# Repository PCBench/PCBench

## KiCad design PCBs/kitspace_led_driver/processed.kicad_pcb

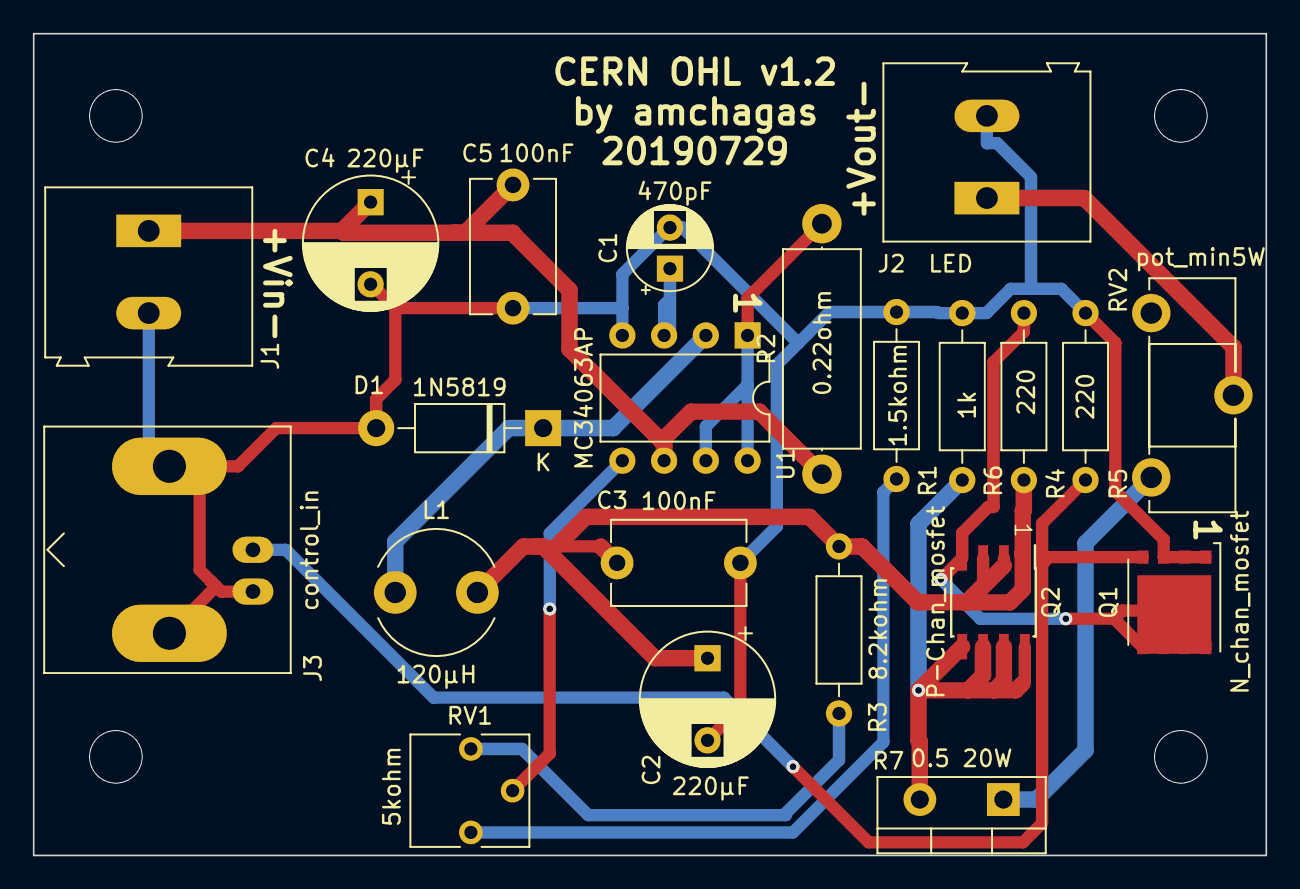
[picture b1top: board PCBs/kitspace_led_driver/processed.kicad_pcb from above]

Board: 2 copper layers, 75.0 x 50.0 mm, 26 parts (0 on the bottom side), 14 nets.

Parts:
C1: 470pF; CP_Radial_D5.0mm_P2.50mm
C2, C4: 220µF; CP_Radial_D8.0mm_P5.00mm
C3, C5: 100nF; C_Disc_D8.0mm_W5.0mm_P7.50mm
D1: 1N5819; D_DO-41_SOD81_P10.16mm_Horizontal
H1, H2, H3, H4: MountingHole; MountingHole_3.2mm_M3
J1: Vin; TerminalBlock_Altech_AK300-2_P5.00mm
J2: LED; TerminalBlock_Altech_AK300-2_P5.00mm
J3: control_in; BNC_Amphenol_B6252HB-NPP3G-50_Horizontal
L1: 120µH; L_Radial_D7.5mm_P5.00mm_Fastron_07P
Q1: N_chan_mosfet; TDSON-8-1
Q2: P-Chan_mosfet; SOIC-8_3.9x4.9mm_P1.27mm
R1: 1.5kohm; R_Axial_DIN0207_L6.3mm_D2.5mm_P10.16mm_Horizontal
R2: 0.22ohm; R_Axial_DIN0414_L11.9mm_D4.5mm_P15.24mm_Horizontal
R3: 8.2kohm; R_Axial_DIN0207_L6.3mm_D2.5mm_P10.16mm_Horizontal
R4, R5: 220; R_Axial_DIN0207_L6.3mm_D2.5mm_P10.16mm_Horizontal
R6: 1k; R_Axial_DIN0207_L6.3mm_D2.5mm_P10.16mm_Horizontal
R7: 0.5 20W; TO-220-2_Vertical
RV1: 5kohm; Potentiometer_Vishay_T73YP_Vertical
RV2: pot_min5W; Potentiometer_ACP_CA14-H5_Horizontal
U1: MC34063AP; DIP-8_W7.62mm

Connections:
GND: C1.2, C2.2, C3.1, C4.2, C5.2, D1.2, J1.2, J2.2, J3.2, Q1.1, Q1.2, Q1.3, R1.2, R5.1, R6.2, U1.4
unnamed: C1.1, U1.3
unnamed: C2.1, C3.2, L1.2, Q2.1, Q2.2, Q2.3, R3.1, R4.2
unnamed: D1.1, L1.1, U1.2
unnamed: J2.1, RV2.2
unnamed: J3.1, Q1.4, R5.2
unnamed: Q1.5, Q2.4, R4.1
unnamed: Q2.5, Q2.6, Q2.7, Q2.8, R6.1, R7.2
unnamed: R1.1, RV1.1
unnamed: R2.2, U1.1, U1.7, U1.8
unnamed: R3.2, RV1.3
unnamed: R7.1, RV2.3
unnamed: RV1.2, U1.5
VDD: C4.1, C5.1, J1.1, R2.1, U1.6

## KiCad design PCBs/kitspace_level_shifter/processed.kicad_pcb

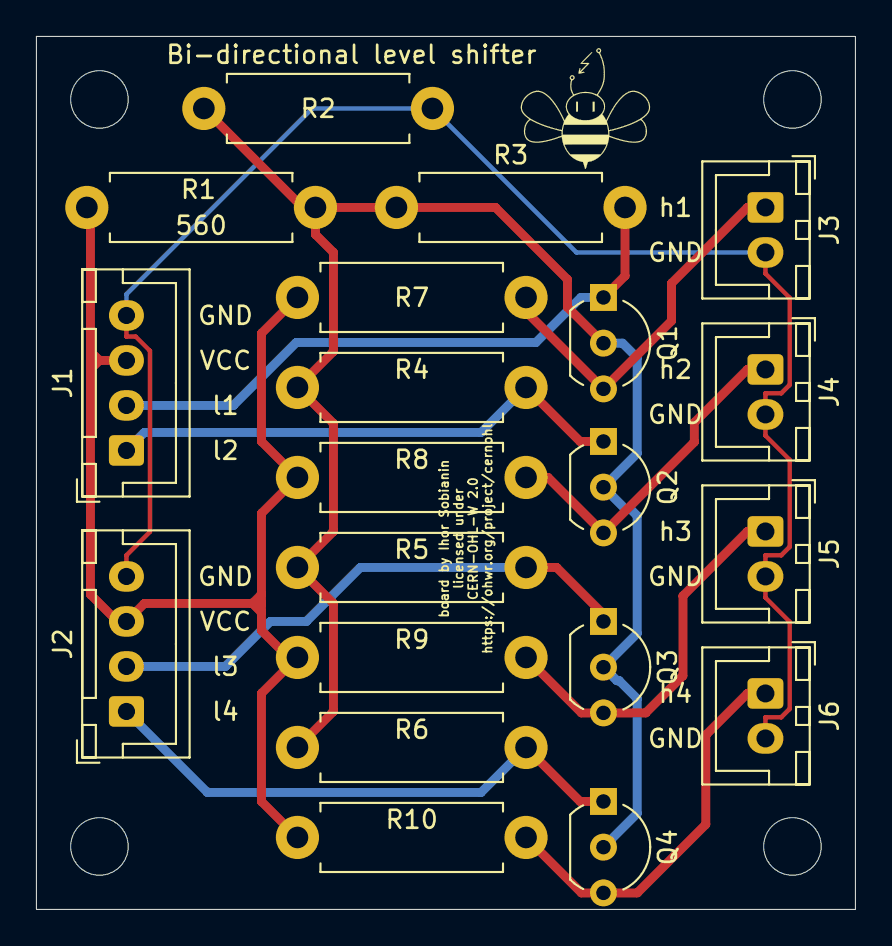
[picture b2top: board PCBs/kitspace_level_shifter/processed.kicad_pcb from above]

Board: 2 copper layers, 45.5 x 48.5 mm, 20 parts (0 on the bottom side), 11 nets.

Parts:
J1, J2: Conn_01x04; JST_XH_B4B-XH-A_1x04_P2.50mm_Vertical
J3, J4, J5, J6: Conn_01x02; JST_XH_B2B-XH-A_1x02_P2.50mm_Vertical
Q1, Q2, Q3, Q4: 2N7000; TO-92_Inline_Wide
R1: 560; R_Axial_DIN0411_L9.9mm_D3.6mm_P12.70mm_Horizontal
R2, R3, R4, R5, R6, R7, R8, R9, R10: 1k; R_Axial_DIN0411_L9.9mm_D3.6mm_P12.70mm_Horizontal

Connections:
+3V3: Q1.2, Q2.2, Q3.2, Q4.2, R1.1, R2.2, R3.1, R4.1, R5.1, R6.1
+5V: J1.3, J2.3, R1.2, R7.1, R8.1, R9.1, R10.1
GND: J1.4, J2.4, J3.2, J4.2, J5.2, J6.2, R2.1
d1_h: J3.1, Q1.3, R7.2
d1_l: J1.2, Q1.1, R3.2
d2_h: J4.1, Q2.3, R8.2
d2_l: J1.1, Q2.1, R4.2
d3_h: J5.1, Q3.3, R9.2
d3_l: J2.2, Q3.1, R5.2
d4_h: J6.1, Q4.3, R10.2
d4_l: J2.1, Q4.1, R6.2

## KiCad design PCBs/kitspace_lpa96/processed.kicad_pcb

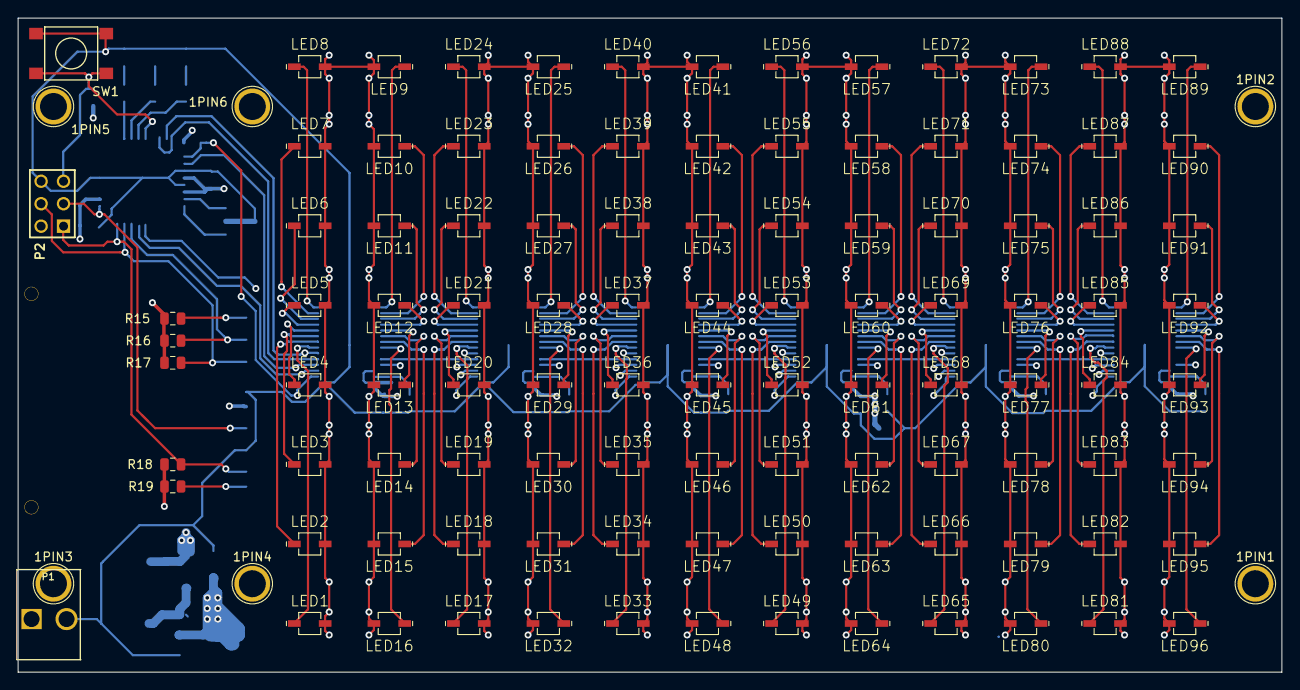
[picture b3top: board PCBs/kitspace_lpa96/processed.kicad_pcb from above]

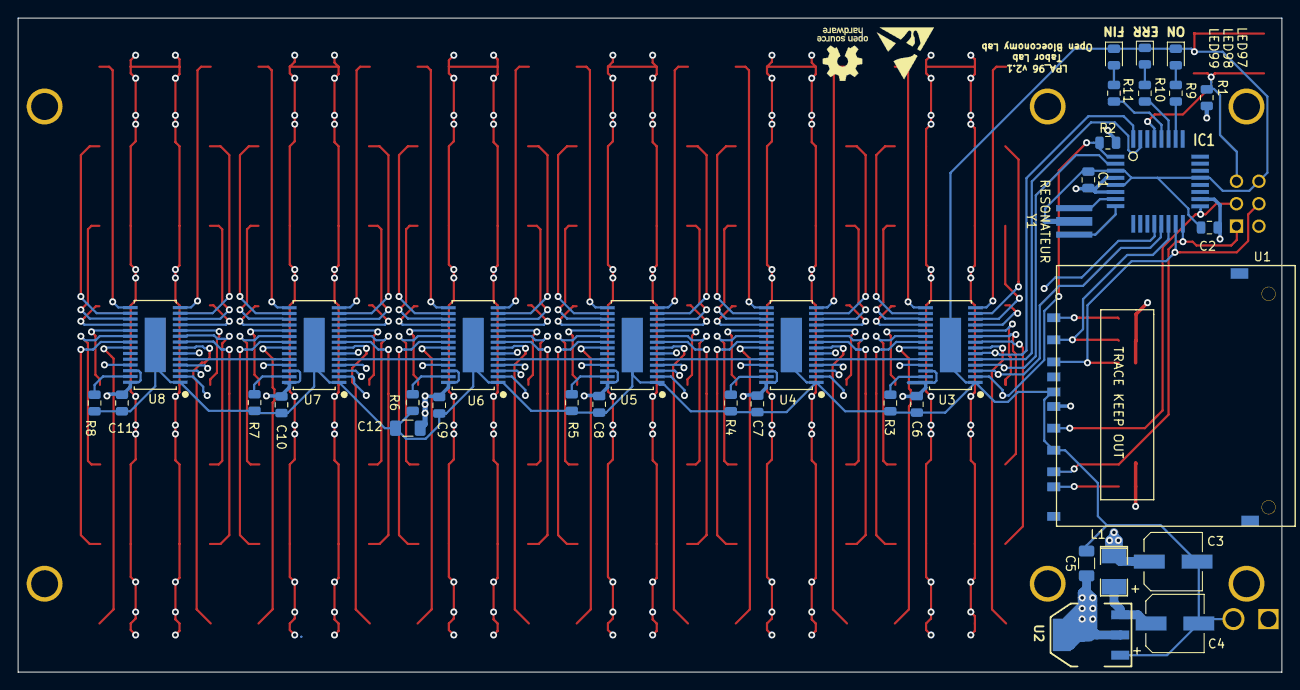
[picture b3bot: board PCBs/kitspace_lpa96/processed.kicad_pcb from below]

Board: 4 copper layers, 143.0 x 74.0 mm, 147 parts (37 on the bottom side), 132 nets.

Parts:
1PIN1, 1PIN2, 1PIN3, 1PIN4, 1PIN5, 1PIN6: P***; 1pin
C1, C2, C6, C7, C8, C9, C10, C11: 100nF; C_0805_2012Metric
C3, C4: 47uF; CP_Elec_6.3x5.3
C5, C12: 10uF; C_1206_3216Metric
IC1: ATMEGA328-A; TQFP32_FIXED
L1: 10uH; L-1210
LED1, LED2, LED3, LED4, LED5, LED6, LED7, LED8, LED9, LED10, LED11, LED12, LED13, LED14, LED15, LED16, LED17, LED18, LED19, LED20, LED21, LED22, LED23, LED24, LED25, LED26, LED27, LED28, LED29, LED30, LED31, LED32, LED33, LED34, LED35, LED36, LED37, LED38, LED39, LED40, LED41, LED42, LED43, LED44, LED45, LED46, LED47, LED48, LED49, LED50, LED51, LED52, LED53, LED54, LED55, LED56, LED57, LED58, LED59, LED60, LED61, LED62, LED63, LED64, LED65, LED66, LED67, LED68, LED69, LED70, LED71, LED72, LED73, LED74, LED75, LED76, LED77, LED78, LED79, LED80, LED81, LED82, LED83, LED84, LED85, LED86, LED87, LED88, LED89, LED90, LED91, LED92, LED93, LED94, LED95, LED96: LED_ALT; VLDx1232G
LED97, LED98, LED99: LED_ALT; LED_0805_2012Metric
P1: CONN_2; PIN_ARRAY_2X1_3960um
P2: CONN_3X2; pin_array_3x2
R1, R2: 10k; R_0805_2012Metric
R3, R4, R5, R6, R7, R8: 2.2k; R_0805_2012Metric
R9, R10, R11: 330R; R_0805_2012Metric
R15, R16, R17, R18, R19: 47k; R_0805_2012Metric
SW1: SW_PUSH; SW_PUSH_SMD
U1: SD_CARD; SD_CONN
U2: LD1117S33; SOT223
U3, U4, U5, U6, U7, U8: TLC5941; TLC5941_PWP_28
Y1: RESONATEUR; crystal_smd

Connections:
/BLANK: IC1.1, R2.1, U3.2, U4.2, U5.2, U6.2, U7.2, U8.2
/ERR: IC1.27, R10.1
/FIN: IC1.28, R11.1
/GSCLK: IC1.12, U3.25, U4.25, U5.25, U6.25, U7.25, U8.25
/MISO: IC1.16, P2.1, R18.2, U1.7
/MODE: IC1.32, U3.6, U4.6, U5.6, U6.6, U7.6, U8.6
/MOSI: IC1.15, P2.4, R17.2, U1.2
/ON: IC1.26, R9.1
/RST: IC1.29, P2.5, R1.1, SW1.1
/SCK: IC1.17, P2.3, U1.5
/SCLK: IC1.2, U3.4, U4.4, U5.4, U6.4, U7.4, U8.4
/SIN: IC1.31, U3.5
/SS: IC1.14, R16.2, U1.1
/VIN: C3.1, L1.1, LED1.2, LED2.2, LED3.2, LED4.2, LED5.2, LED6.2, LED7.2, LED8.2, LED9.2, LED10.2, LED11.2, LED12.2, LED13.2, LED14.2, LED15.2, LED16.2, LED17.2, LED18.2, LED19.2, LED20.2, LED21.2, LED22.2, LED23.2, LED24.2, LED25.2, LED26.2, LED27.2, LED28.2, LED29.2, LED30.2, LED31.2, LED32.2, LED33.2, LED34.2, LED35.2, LED36.2, LED37.2, LED38.2, LED39.2, LED40.2, LED41.2, LED42.2, LED43.2, LED44.2, LED45.2, LED46.2, LED47.2, LED48.2, LED49.2, LED50.2, LED51.2, LED52.2, LED53.2, LED54.2, LED55.2, LED56.2, LED57.2, LED58.2, LED59.2, LED60.2, LED61.2, LED62.2, LED63.2, LED64.2, LED65.2, LED66.2, LED67.2, LED68.2, LED69.2, LED70.2, LED71.2, LED72.2, LED73.2, LED74.2, LED75.2, LED76.2, LED77.2, LED78.2, LED79.2, LED80.2, LED81.2, LED82.2, LED83.2, LED84.2, LED85.2, LED86.2, LED87.2, LED88.2, LED89.2, LED90.2, LED91.2, LED92.2, LED93.2, LED94.2, LED95.2, LED96.2, P1.1
/XLAT: IC1.13, U3.3, U4.3, U5.3, U6.3, U7.3, U8.3
/lpa96_leds_drivers/SOUT1: U3.24, U4.5
/lpa96_leds_drivers/SOUT2: U4.24, U5.5
/lpa96_leds_drivers/SOUT3: U5.24, U6.5
/lpa96_leds_drivers/SOUT4: U6.24, U7.5
/lpa96_leds_drivers/SOUT5: U7.24, U8.5
GND: C1.1, C2.1, C3.2, C4.2, C5.2, C6.2, C7.2, C8.2, C9.2, C10.2, C11.2, C12.2, IC1.3, IC1.5, IC1.21, LED97.1, LED98.1, LED99.1, P1.2, P2.6, R3.1, R4.1, R5.1, R6.1, R7.1, R8.1, SW1.2, U1.3, U1.6, U2.1, U3.1, U3.29, U4.1, U4.29, U5.1, U5.29, U6.1, U6.29, U7.1, U7.29, U8.1, U8.29, Y1.2
unnamed: C4.1, L1.2, U2.3
unnamed: IC1.7, Y1.3
unnamed: IC1.8, Y1.1
unnamed: LED1.1, U3.7
unnamed: LED2.1, U3.8
unnamed: LED3.1, U3.9
unnamed: LED4.1, U3.10
unnamed: LED5.1, U3.11
unnamed: LED6.1, U3.12
unnamed: LED7.1, U3.13
unnamed: LED8.1, U3.14
unnamed: LED9.1, U3.15
unnamed: LED10.1, U3.16
unnamed: LED11.1, U3.17
unnamed: LED12.1, U3.18
unnamed: LED13.1, U3.19
unnamed: LED14.1, U3.20
unnamed: LED15.1, U3.21
unnamed: LED16.1, U3.22
unnamed: LED17.1, U4.7
unnamed: LED18.1, U4.8
unnamed: LED19.1, U4.9
unnamed: LED20.1, U4.10
unnamed: LED21.1, U4.11
unnamed: LED22.1, U4.12
unnamed: LED23.1, U4.13
unnamed: LED24.1, U4.14
unnamed: LED25.1, U4.15
unnamed: LED26.1, U4.16
unnamed: LED27.1, U4.17
unnamed: LED28.1, U4.18
unnamed: LED29.1, U4.19
unnamed: LED30.1, U4.20
unnamed: LED31.1, U4.21
unnamed: LED32.1, U4.22
unnamed: LED33.1, U5.7
unnamed: LED34.1, U5.8
unnamed: LED35.1, U5.9
unnamed: LED36.1, U5.10
unnamed: LED37.1, U5.11
unnamed: LED38.1, U5.12
unnamed: LED39.1, U5.13
unnamed: LED40.1, U5.14
unnamed: LED41.1, U5.15
unnamed: LED42.1, U5.16
unnamed: LED43.1, U5.17
unnamed: LED44.1, U5.18
unnamed: LED45.1, U5.19
unnamed: LED46.1, U5.20
unnamed: LED47.1, U5.21
unnamed: LED48.1, U5.22
unnamed: LED49.1, U6.7
unnamed: LED50.1, U6.8
unnamed: LED51.1, U6.9
unnamed: LED52.1, U6.10
unnamed: LED53.1, U6.11
unnamed: LED54.1, U6.12
unnamed: LED55.1, U6.13
unnamed: LED56.1, U6.14
unnamed: LED57.1, U6.15
unnamed: LED58.1, U6.16
unnamed: LED59.1, U6.17
unnamed: LED60.1, U6.18
unnamed: LED61.1, U6.19
unnamed: LED62.1, U6.20
unnamed: LED63.1, U6.21
unnamed: LED64.1, U6.22
unnamed: LED65.1, U7.7
unnamed: LED66.1, U7.8
unnamed: LED67.1, U7.9
unnamed: LED68.1, U7.10
unnamed: LED69.1, U7.11
unnamed: LED70.1, U7.12
unnamed: LED71.1, U7.13
unnamed: LED72.1, U7.14
unnamed: LED73.1, U7.15
unnamed: LED74.1, U7.16
unnamed: LED75.1, U7.17
unnamed: LED76.1, U7.18
unnamed: LED77.1, U7.19
unnamed: LED78.1, U7.20
unnamed: LED79.1, U7.21
unnamed: LED80.1, U7.22
unnamed: LED81.1, U8.7
unnamed: LED82.1, U8.8
unnamed: LED83.1, U8.9
unnamed: LED84.1, U8.10
unnamed: LED85.1, U8.11
unnamed: LED86.1, U8.12
unnamed: LED87.1, U8.13
unnamed: LED88.1, U8.14
unnamed: LED89.1, U8.15
unnamed: LED90.1, U8.16
unnamed: LED91.1, U8.17
unnamed: LED92.1, U8.18
unnamed: LED93.1, U8.19
unnamed: LED94.1, U8.20
unnamed: LED95.1, U8.21
unnamed: LED96.1, U8.22
unnamed: LED97.2, R9.2
unnamed: LED98.2, R10.2
unnamed: LED99.2, R11.2
unnamed: R3.2, U3.27
unnamed: R4.2, U4.27
unnamed: R5.2, U5.27
unnamed: R6.2, U6.27
unnamed: R7.2, U7.27
unnamed: R8.2, U8.27
unnamed: R15.2, U1.9
unnamed: R19.2, U1.8
VCC: C1.2, C2.2, C5.1, C6.1, C7.1, C8.1, C9.1, C10.1, C11.1, C12.1, IC1.4, IC1.6, IC1.18, P2.2, R1.2, R2.2, R15.1, R16.1, R17.1, R18.1, R19.1, U1.4, U2.2, U2.4, U3.26, U3.28, U4.26, U4.28, U5.26, U5.28, U6.26, U6.28, U7.26, U7.28, U8.26, U8.28

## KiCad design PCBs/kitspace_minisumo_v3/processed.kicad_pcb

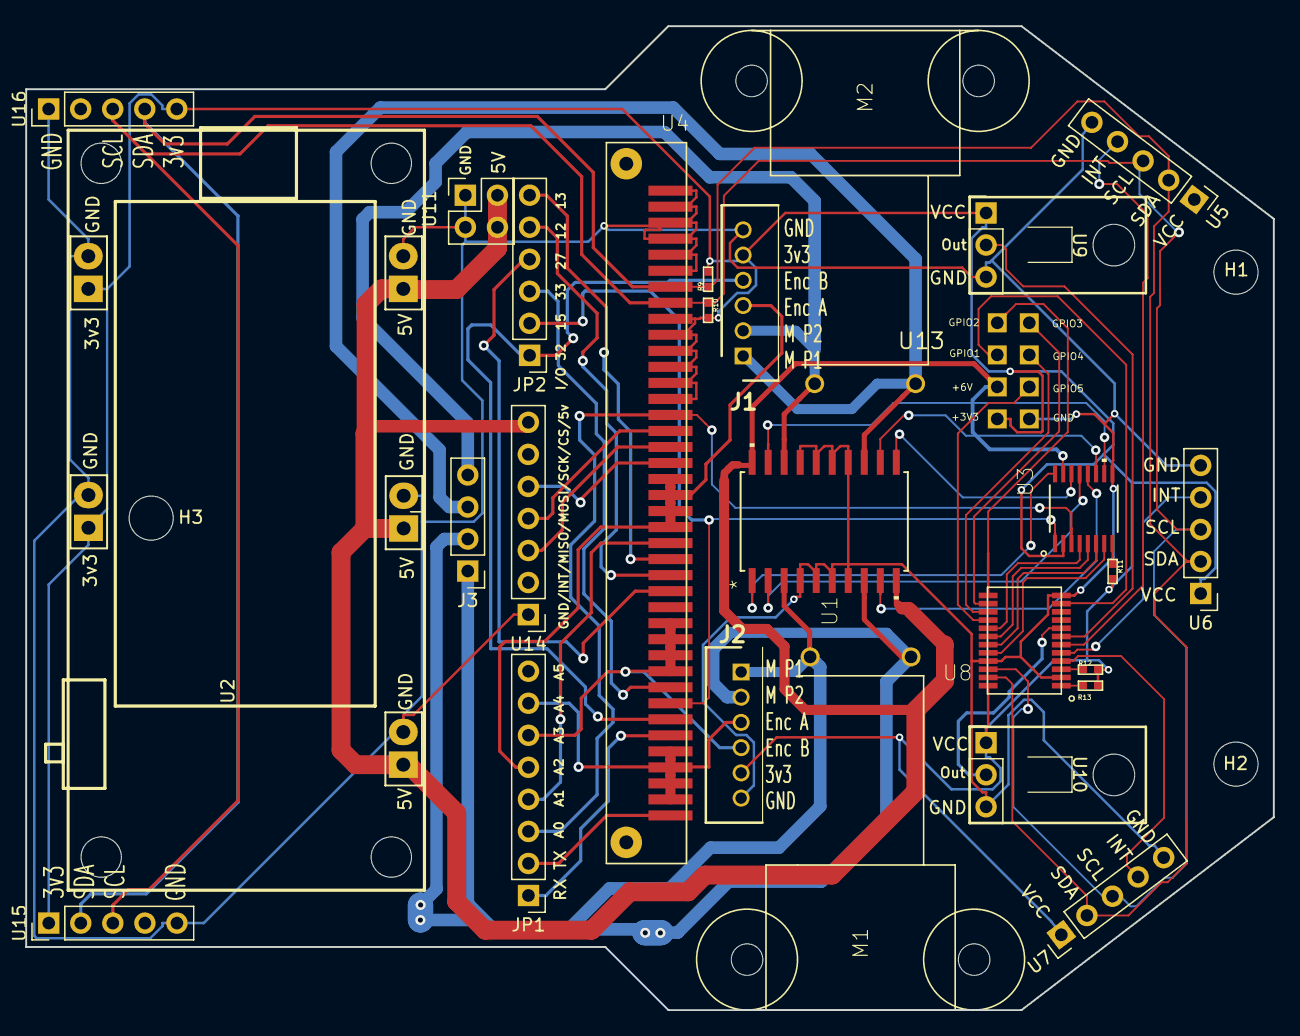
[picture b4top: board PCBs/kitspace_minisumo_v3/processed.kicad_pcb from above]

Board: 2 copper layers, 98.9 x 78.0 mm, 30 parts (0 on the bottom side), 48 nets.

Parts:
H1, H2, H3: MountingHole; MountingHole_3.5mm
J1: Right Motor; SHDR6W50P0X200_1X6_1390X450X600P
J2: Left Motor; SHDR6W50P0X200_1X6_1390X450X600P
J3: Motor Connector2; PinHeader_1x04_P2.54mm_Vertical
JP1: Conn_01x08; PinHeader_1x08_P2.54mm_Vertical
JP2: Conn_01x06; PinHeader_1x06_P2.54mm_Vertical
M1, M2: N20_MOTOR; N20-MOTOR-BRACKET
R9, R10, R11, R12, R13: 10k; RES_0402
U1: L293DD; SO-20
U2: 16340_Battery_Module; 16340 Battery Module
U3: TXB0106PWRPW16-L; PW16-L
U4: BBC Micro:bit; CYCLONE_MICROBIT_VERTICAL
U5: VL53L1X Right; PinHeader_1x05_P2.54mm_Vertical
U6: VL53L1X Center; PinHeader_1x05_P2.54mm_Vertical
U7: VL53L1X Left; PinHeader_1x05_P2.54mm_Vertical
U8: TCA9539PWR; 24-TSSOP
U9: NW; SparkFun QRE1113
U10: NE; SparkFun QRE1113
U11: Conn_02x02_Top_Bottom; PinHeader_2x02_P2.54mm_Vertical
U13: SUMO_IO
U14: Conn_01x07; PinHeader_1x07_P2.54mm_Vertical
U15, U16: Conn_01x05_2; PinHeader_1x05_P2.54mm_Vertical

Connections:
+3V3: J1.5, J2.5, R9.P$2, R10.P$2, R11.P$2, R12.P$2, R13.P$2, U2.3, U3.2, U4.3.3V@9, U4.3.3V@10, U4.3.3V@11, U4.3.3V@12, U4.3.3V@13, U4.3.3V@14, U6.1, U7.1, U8.24, U9.+3V3, U10.+3V3, U13.3V3, U15.1, U16.5
+5V: U1.10, U1.20, U2.1, U3.15, U11.2, U11.4, U13.6V, U14.7
/INPUT_1: U3.4, U8.17
/INPUT_2: U3.5, U8.18
/INPUT_3: U3.6, U8.19
/INPUT_4: U3.7, U8.20
/IO1: U8.11, U13.GPIO1
/IO2: U8.13, U13.GPIO2
/IO3: U8.14, U13.GPIO3
/IO4: U8.15, U13.GPIO4
/IO5: U8.16, U13.GPIO5
/ML1: J2.1, J3.1, M1.1, U1.3
/ML2: J2.2, J3.2, M1.2, U1.8
/MR1: J1.1, J3.3, M2.1, U1.13
/MR2: J1.2, J3.4, M2.2, U1.18
/NE: U8.8, U10.SIGNAL
/NW: U8.7, U9.SIGNAL
/XS1: U7.4, U8.4
/XS2: U6.4, U8.5
/XS3: U5.4, U8.6
A0: JP1.3, U3.3, U4.P16
A1: JP1.4, U4.RESERVED
A2: J1.3, JP1.5, U4.P2_ANALOG_IN@19, U4.P2_ANALOG_IN@20, U4.P2_ANALOG_IN@21, U4.P2_ANALOG_IN@22
A3: J2.4, JP1.6, U4.P1_ANALOG_IN@28, U4.P1_ANALOG_IN@29, U4.P1_ANALOG_IN@30, U4.P1_ANALOG_IN@31
A4: J2.3, JP1.7, U4.P0_ANALOG_IN@36, U4.P0_ANALOG_IN@37, U4.P0_ANALOG_IN@38, U4.P0_ANALOG_IN@39
GND: J1.6, J2.6, U1.4, U1.5, U1.6, U1.7, U1.14, U1.15, U1.16, U1.17, U2.2, U2.4, U3.9, U4.GND@1, U4.GND@2, U4.GND@3, U4.GND@4, U4.GND@5, U4.GND@6, U5.5, U6.5, U7.5, U8.2, U8.12, U8.21, U9.GND, U10.GND, U11.1, U11.3, U13.GND, U14.1, U15.5, U16.1
IO12: JP2.5, U4.P10_LED_COL_3_ANALO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
IO13: JP2.6, U4.P11_BUTTON_B
IO15: JP2.2, U3.1, U4.P6_LED_COL_9
IO16: JP1.1, U4.P4_LED_COL_2_ANALOG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
IO17: JP1.2, U4.P3_LED_COL_1_ANALOG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
IO27: JP2.4, U4.P9_LED_COL_7
IO32: J1.4, JP2.1, U4.P5_BUTTON_A
IO33: JP2.3, U4.P7_LED_COL8
MISO: U4.P14_MISO, U14.3
MOSI: U4.P15_MOSI, U14.4
unnamed: R11.P$1, U3.8
unnamed: R12.P$1, U8.3
unnamed: R13.P$1, U8.1
unnamed: U1.1, U3.16
unnamed: U1.2, U3.13
unnamed: U1.9, U3.12
unnamed: U1.11, U3.14
unnamed: U1.12, U3.11
unnamed: U1.19, U3.10
SCK: U4.P13_SCK, U14.5
SCL: R10.P$1, U4.P21_SCL, U5.3, U6.3, U7.3, U8.22, U15.3, U16.3
SDA: R9.P$1, U4.P20_SDA, U5.2, U6.2, U7.2, U8.23, U15.2, U16.4

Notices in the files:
PCBs/kitspace_led_driver/processed.kicad_pcb:
CERN OHL v1.2
PCBs/kitspace_level_shifter/processed.kicad_pcb:
licensed under
CERN-OHL-W 2.0
PCBs/kitspace_minisumo_v3/processed.kicad_pcb:
CERN-OHl-P
